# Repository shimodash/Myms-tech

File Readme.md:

# 自己紹介

Welcome Myms-tech website!

湘南・鎌倉エリアの技術教育ボランティアです。

古都鎌倉の子どもたち科学好きな子に！

[website](https://shimodash.github.io/Myms-tech)

# 作品
[paperplane](./paperplane/paperplane.pdf)

# リンク
[Facebook](https://www.facebook.com/mymstech)

[NEKTON大船](http://www.nespa-ad.co.jp/nekton/)

# お問い合わせ
[mail](mailto:sbt.shimoda@gmail.com)

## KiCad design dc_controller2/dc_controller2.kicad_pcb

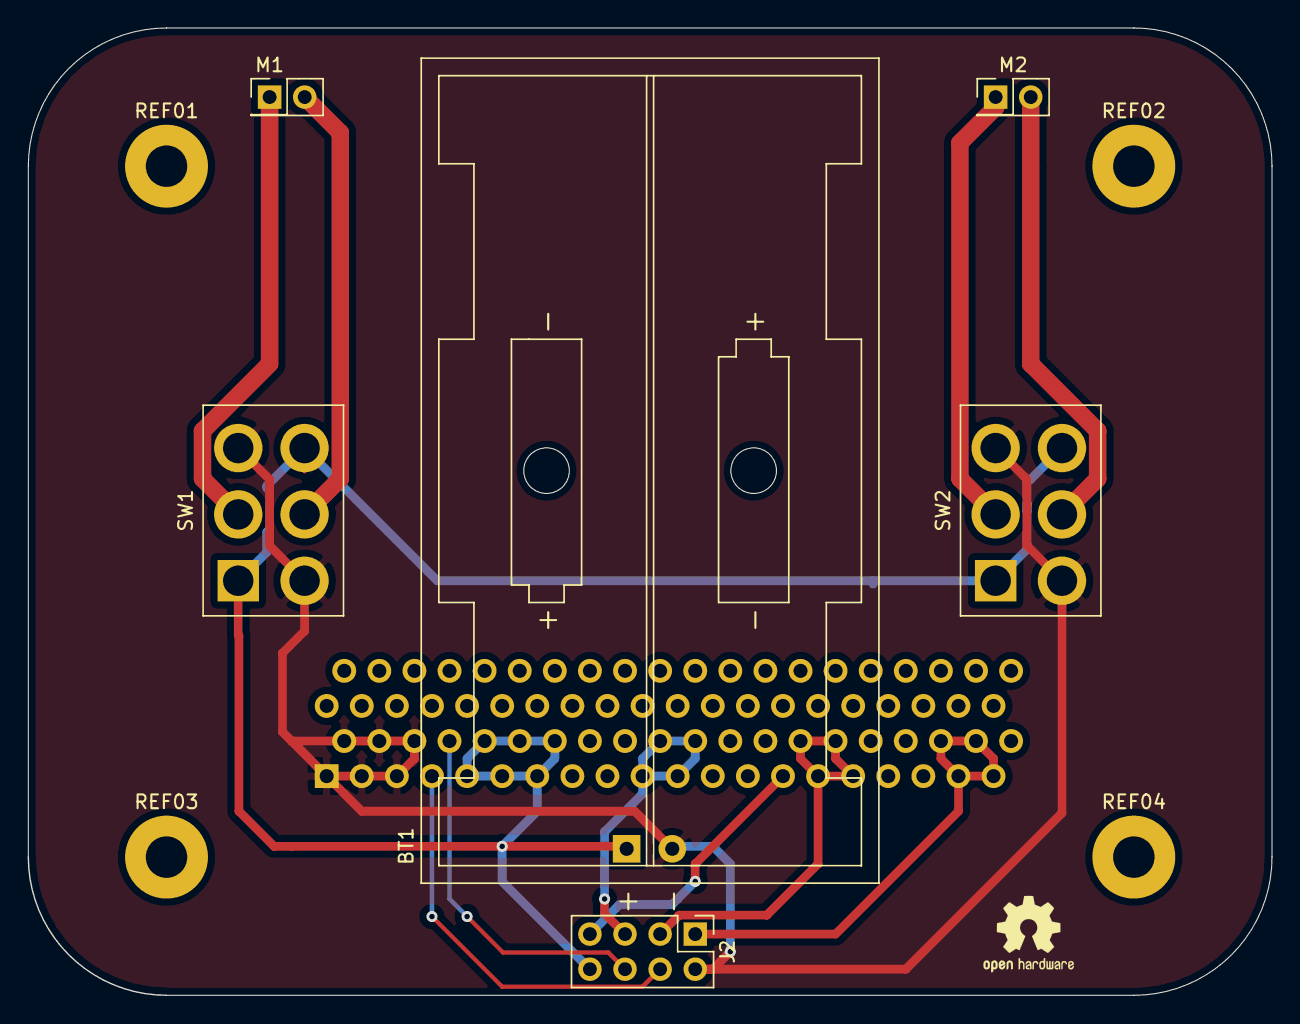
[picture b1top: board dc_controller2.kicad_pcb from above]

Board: 2 copper layers, 90.0 x 70.0 mm, 11 parts (1 on the bottom side), 12 nets.

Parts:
BT1: Battery; BatteryHolder_myfoot_2xAA
J1: microbit_edge_connector; 4UCON_17909_02x401.27mm_Vertical
J2: Conn_02x04_Top_Bottom; PinHeader_2x04_P2.54mm_Vertical
M1, M2: Motor_DC; PinHeader_2x01_P2.54mm_Vertical
REF01, REF02, REF03, REF04: MountingHole_3mm_Pad
SW1, SW2: SW_Push_DPDT; toggle_sw_THT

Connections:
+3V0: BT1.1, J1.17, J1.19, J1.21, J1.23, J1.25, J1.27, J2.8, SW1.1, SW1.6, SW2.1, SW2.6
GND: BT1.2, J1.1, J1.3, J1.5, J1.7, J1.9, J1.11, J2.2, SW1.3, SW1.4, SW2.3, SW2.4
unnamed: J1.13, J2.4
unnamed: J1.15, J2.6
unnamed: J1.37, J1.39, J1.41, J1.43, J2.5
unnamed: J1.53, J2.7
unnamed: J1.55, J1.57, J1.59, J1.61, J2.3
unnamed: J1.71, J1.73, J1.75, J1.77, J2.1
unnamed: M1.1, SW1.2
unnamed: M1.2, SW1.5
unnamed: M2.1, SW2.2
unnamed: M2.2, SW2.5

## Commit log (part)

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2020-04-25 paperplane commit
2020-04-25 initial
2020-06-27 dc motor control data commit
2020-06-27 基板についてのコメントを追加
2020-07-04 library file commit
2020-07-04 path change
2020-08-09 readme.md update
2020-08-09 image add
2020-08-09 animation gif sample
2020-08-10 web page
2020-08-13 update explanation
2020-08-15 dropdown and navbar change
2020-08-28 slide photo update
2020-09-12 ワークショップイベント結果を更新
2020-09-12 ワークショップ結果の更新
2020-09-12 2019 collapse
2020-10-02 2020workshop写真追加
2020-10-02 file link add
2020-10-03 D2-1 ctrl
2020-10-10 M5atom sample ir & BLE keyboard add
2020-10-30 mail address fix
2020-11-03 website add
2020-11-22 lcd st7789 sample sketch
2020-11-25 profile文の修正
2020-12-19 リンクにインテル鎌倉さんを追加
2020-12-31 font change
2021-01-31 nfc sample add
2021-02-11 Create BLE_MIDI_sample.ino
    ESP32でのBLEでMIDIデータ送信サンプル
2021-02-23 back ground color change
2021-03-07 team namge change
2021-06-26 FY2021のイベントを更新
2021-07-01 neopixel panel program add
2021-07-21 scratch cm frame add
2021-09-04 m5stick boot file commit
2021-09-23 2021 event report
2021-09-23 images/2021workshop.png
2021-09-23 fix image link bug
2022-07-30 2022 0727 workshop add
2022-07-30 20220727 work shop add
2022-07-30 photo update
2022-09-03 2022 2nd commit
2022-09-19 add link ekidenproject.jp
2024-07-13 M5JCC2024 add
2024-07-13 m5atom and spresense sketch add
2024-07-13 delet file
2024-07-13 Readme add
2024-07-13 stl file add readme update
2025-01-01 logo-file upload for PCB and 3D design
2025-01-03 update test
2025-01-03 update svg file
2025-08-31 Add files via upload
    Arduinoのスケッチとゲーム用の画像をアップロード
2025-09-05 result playtime change
2025-09-15 light-frame data commit
    from DAISO RECHAGABLE COB LIGHT JAN 4971275815278
2025-09-15 light-frame cover data commit
    from DAISO RECHAGABLE COB LIGHT JAN 4971275815278
2026-04-12 Add files via upload
    参照先のデータはこちらです。
    https://www.thingiverse.com/thing:6957687
2026-04-25 Rename REDME.md to README.md
2026-04-25 Rename Readme.md to README.md
2026-05-06 Add Stack-chan style face sketch for SubCore1
